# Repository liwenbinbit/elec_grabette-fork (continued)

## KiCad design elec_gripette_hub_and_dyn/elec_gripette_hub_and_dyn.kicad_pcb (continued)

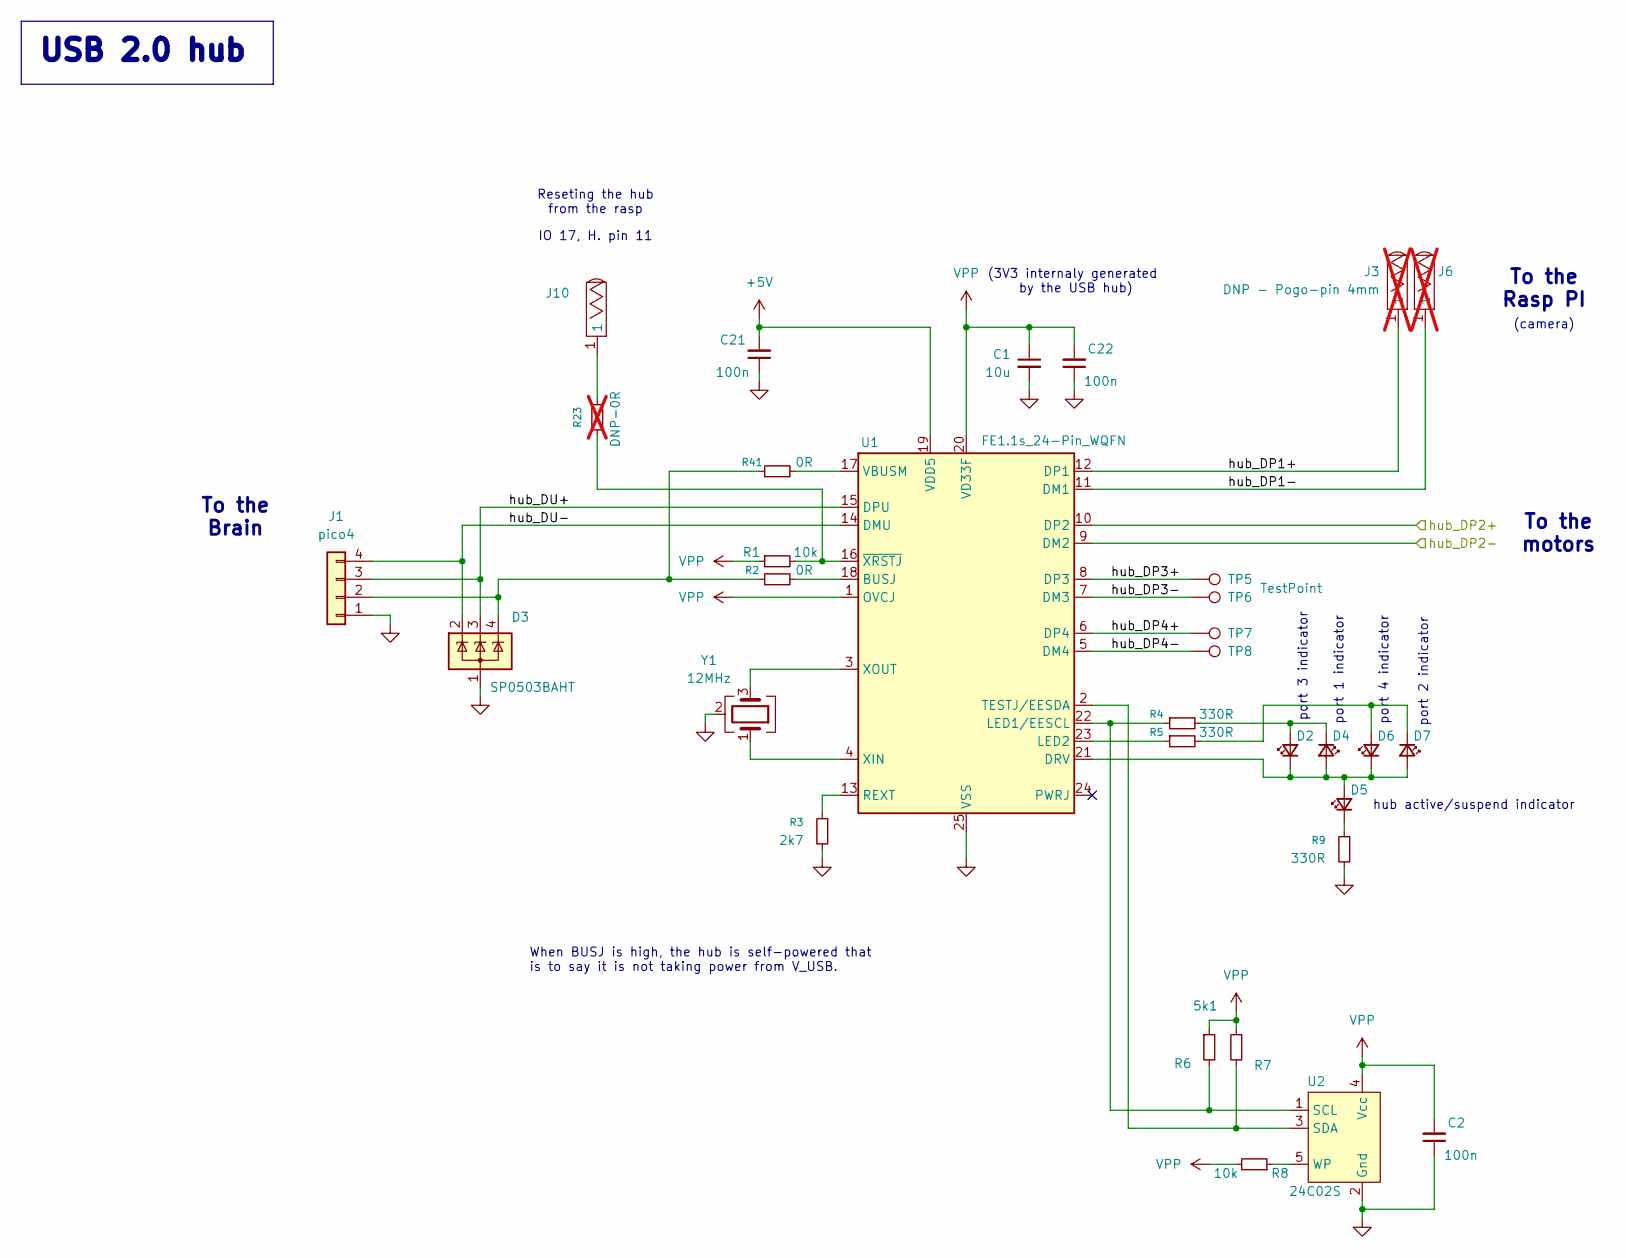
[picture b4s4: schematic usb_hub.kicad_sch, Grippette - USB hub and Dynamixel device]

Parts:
C1: 10u; C_0603_1608Metric; LCSC Part C1691
C2, C21, C22: 100n; C_0603_1608Metric; LCSC Part C85864
D2, D4, D6, D7: LED_Small; LED_0603_1608Metric; LCSC Part C7429915
D3: SP0503BAHT; SOT-143; LCSC Part C41364459
D5: LED_Small; LED_0603_1608Metric; LCSC Part C19171301
J1: pico4; Molex_PicoBlade_53047-0410_1x04_P1.25mm_Vertical; LCSC Part C504989
J3, J6: DNP - Pogo-pin 4mm; CONN-TH_YZ95315064P-01_pogo; LCSC Part C5157245; not fitted
J10: Pogo-pin 4mm; CONN-TH_YZ95315064P-01_pogo; LCSC Part C5157245
R1, R8: 10k; R_0402_1005Metric; LCSC Part C25744
R2, R41: 0R; R_0402_1005Metric; LCSC Part C17168
R3: 2k7; R_0402_1005Metric; LCSC Part C138017
R4, R5, R9: 330R; R_0402_1005Metric; LCSC Part C105875
R6, R7: 5k1; R_0402_1005Metric; LCSC Part C25905
R23: DNP-0R; R_0603_1608Metric; not fitted
TP5, TP6, TP7, TP8: TestPoint; TestPoint_Pad_D1.0mm
U1: FE1.1s_24-Pin_WQFN; WQFN-24-1EP_4x4mm_P0.5mm_EP2.6x2.6mm; LCSC Part C6776948
U2: 24C02S; SOT-23-5; LCSC Part C18723540
Y1: 12MHz; Crystal_SMD_3225-4Pin_3.2x2.5mm; LCSC Part C133334

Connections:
+5V: C21.2, U1.19 (VDD5); also elsewhere on the board
/Dynamixel-TTL over USB/hub_DP2+: U1.10 (DP2); also elsewhere on the board
/Dynamixel-TTL over USB/hub_DP2-: U1.9 (DM2); also elsewhere on the board
/USB hub/hub_DP1+: J3.1, U1.12 (DP1)
/USB hub/hub_DP1-: J6.1, U1.11 (DM1)
/USB hub/hub_DP3+: TP5.1, U1.8 (DP3)
/USB hub/hub_DP3-: TP6.1, U1.7 (DM3)
/USB hub/hub_DP4+: TP7.1, U1.6 (DP4)
/USB hub/hub_DP4-: TP8.1, U1.5 (DM4)
/USB hub/hub_DU+: D3.3 (K), J1.3, U1.15 (DPU)
/USB hub/hub_DU-: D3.2 (K), J1.4, U1.14 (DMU)
GND: C1.2, C2.1, C21.1, C22.1, D3.1 (A), J1.1, R3.2, R9.2, U1.25 (VSS), U2.2 (Gnd), Y1.2 (G), Y1.4 (G); also elsewhere on the board
unnamed: D2.2 (A), D4.1 (K), R4.2
unnamed: D2.1 (K), D4.2 (A), D5.2 (A), D6.1 (K), D7.2 (A), U1.21 (DRV)
unnamed: D5.1 (K), R9.1
unnamed: D6.2 (A), D7.1 (K), R5.2
unnamed: D3.4 (K), J1.2, R2.1, R41.1
unnamed: J10.1, R23.2
unnamed: R2.2, U1.18 (BUSJ)
unnamed: R4.1, R6.2, U1.22 (LED1/EESCL), U2.1 (SCL)
unnamed: R5.1, U1.23 (LED2)
unnamed: R3.1, U1.13 (REXT)
unnamed: R7.2, U1.2 (TESTJ/EESDA), U2.3 (SDA)
unnamed: R41.2, U1.17 (VBUSM)
unnamed: U1.4 (XIN), Y1.1
unnamed: U1.3 (XOUT), Y1.3
unnamed: R1.2, R23.1, U1.16 (~XRSTJ)
unnamed: R8.1, U2.5 (WP)
VPP: C1.1, C2.2, C22.2, R1.1, R6.1, R7.1, R8.2, U1.1 (OVCJ), U1.20 (VD33F), U2.4 (Vcc)

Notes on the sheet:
To the motors
port 4 indicator
When BUSJ is high, the hub is self-powered that is to say it is not taking power from V_USB.
port 2 indicator
port 3 indicator
To the Rasp PI
(3V3 internaly generated by the USB hub)
Reseting the hub from the rasp
(camera)
port 1 indicator
IO 17, H. pin 11
hub active/suspend indicator
To the Brain
USB 2.0 hub

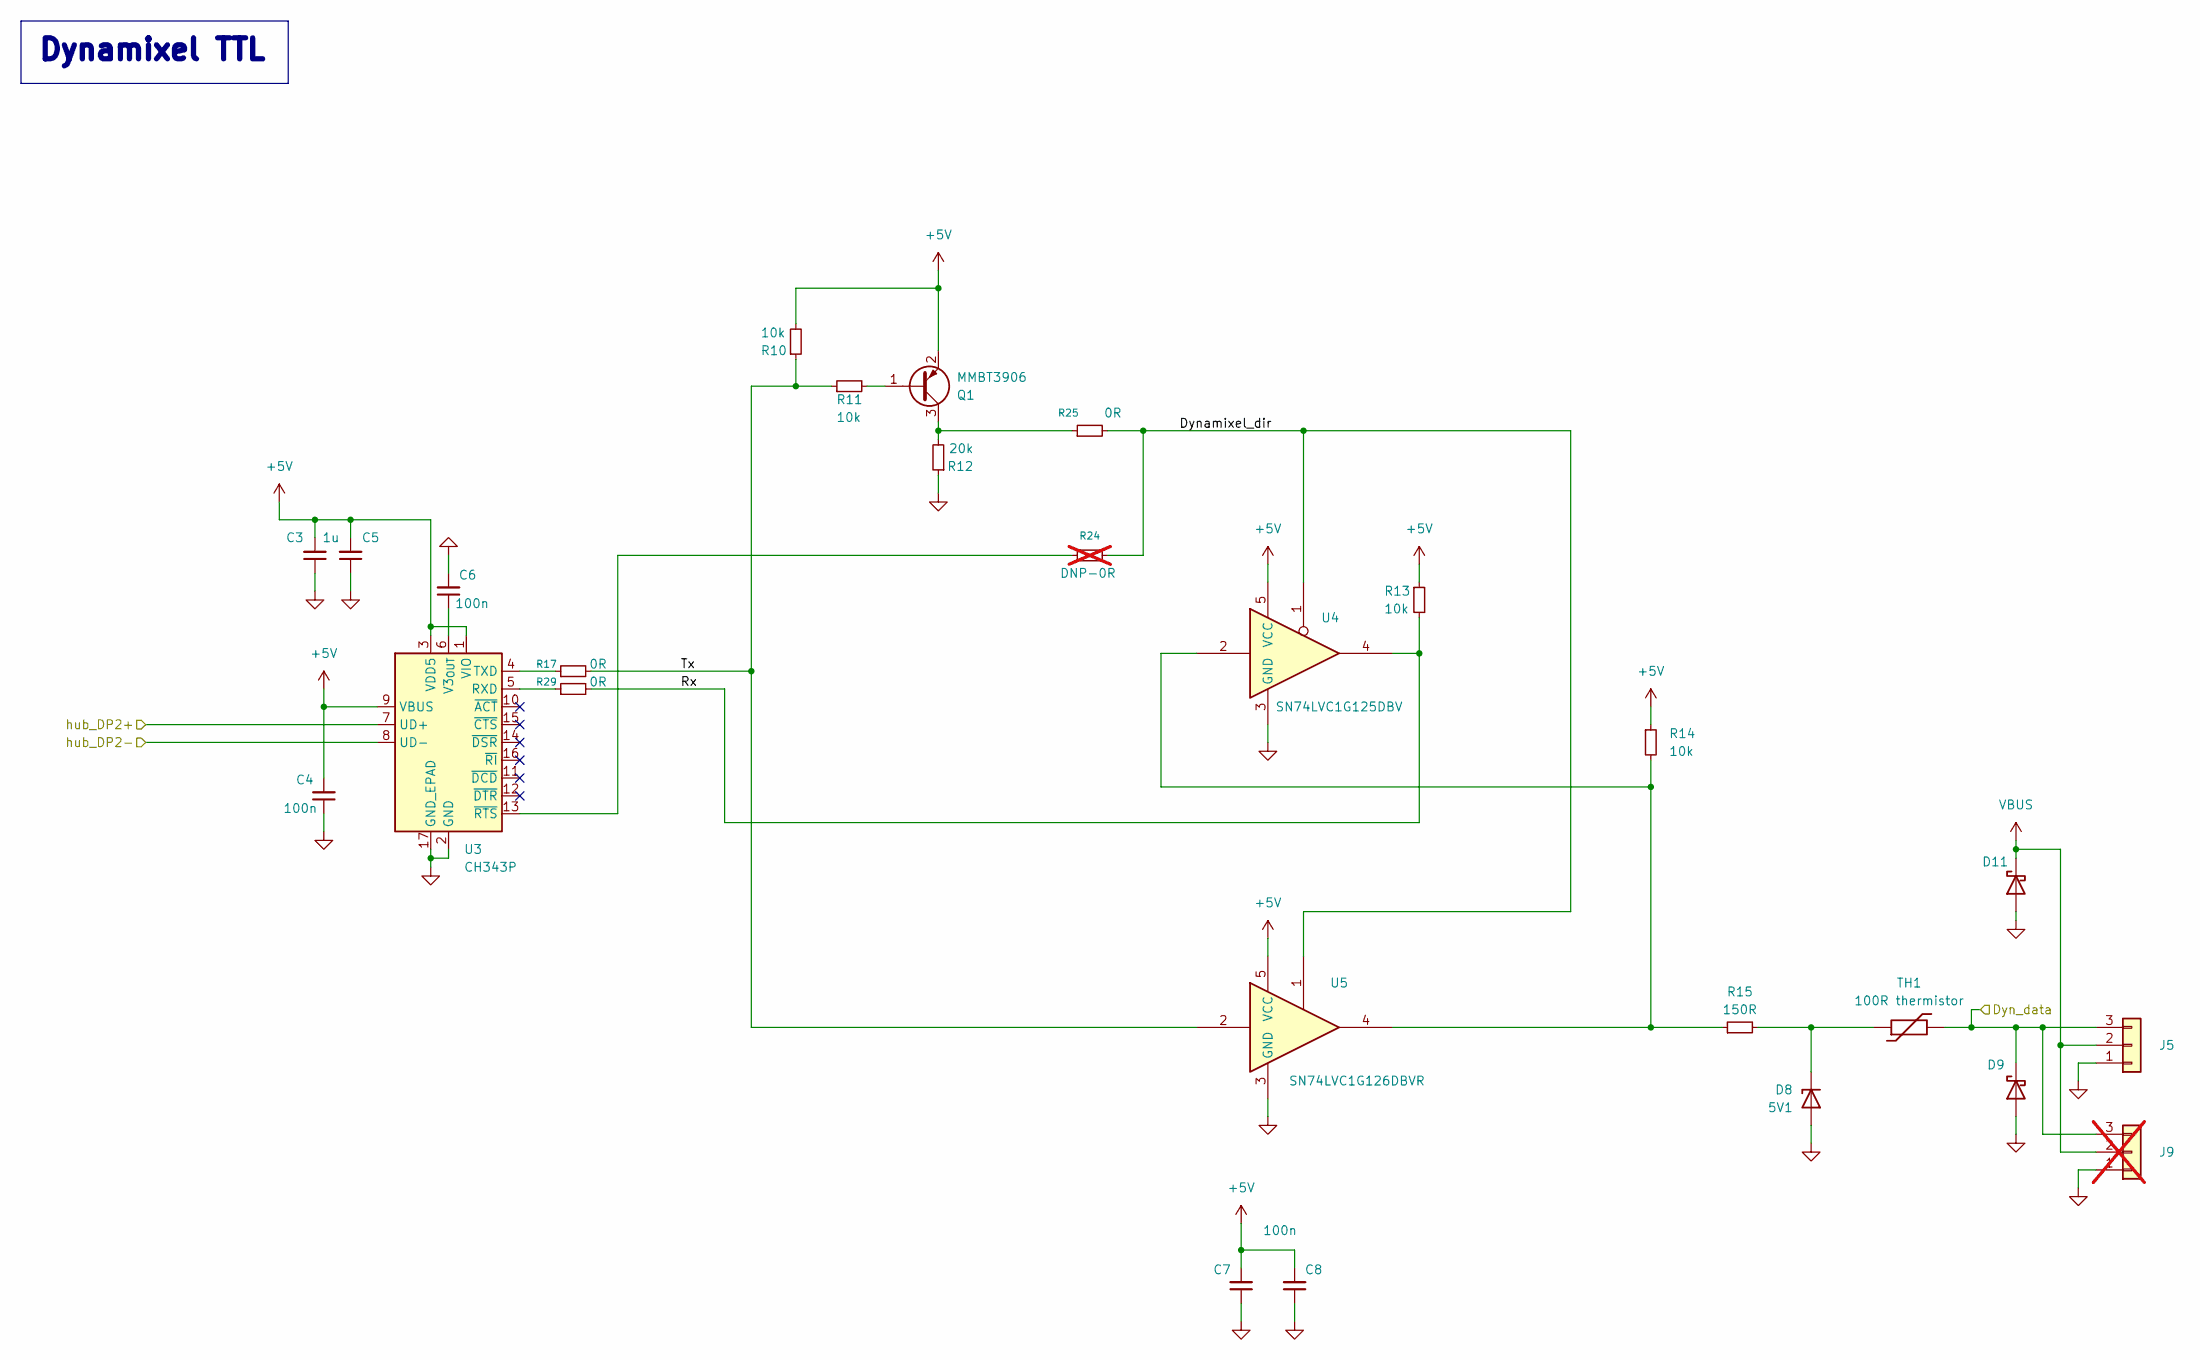
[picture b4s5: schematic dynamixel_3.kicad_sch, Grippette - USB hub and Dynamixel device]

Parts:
C3, C5: 1u; C_0603_1608Metric; LCSC Part C1592
C4, C6, C7, C8: 100n; C_0603_1608Metric; LCSC Part C85864
D8: 5V1; D_SOD-323; LCSC Part C151348
D9, D11: B5819WS; D_SOD-323; LCSC Part C64886
J5: Feetech; Molex_SPOX_5267-03A_1x03_P2.50mm_Vertical; LCSC Part C293315
J9: Feetech; Molex_SPOX_5267-03A_1x03_P2.50mm_Vertical; not fitted
Q1: MMBT3906; SOT-23; LCSC Part C727128
R10, R11, R13, R14: 10k; R_0402_1005Metric; LCSC Part C25744
R12: 20k; R_0402_1005Metric; LCSC Part C2906867
R15: 150R; R_0402_1005Metric; LCSC Part C138054
R17, R25, R29: 0R; R_0402_1005Metric; LCSC Part C17168
R24: DNP-0R; R_0603_1608Metric; not fitted
TH1: 100R thermistor; R_0603_1608Metric; LCSC Part C913703
U3: CH343P; WCH_QFN-16-1EP_3x3mm_P0.5mm_EP1.8x1.8mm; LCSC Part C2846043
U4: SN74LVC1G125DBV; SOT-23-5; LCSC Part C23654
U5: SN74LVC1G126DBVR; SOT-23-5; LCSC Part C7834

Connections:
+5V: C3.2, C4.2, C5.2, C7.2, C8.2, Q1.2 (E), R10.2, R13.1, R14.1, U3.1 (VIO), U3.3 (VDD5), U3.9 (VBUS), U4.5 (VCC), U5.5 (VCC); also elsewhere on the board
/Dynamixel-TTL over USB/Dyn_data: D9.1 (K), J5.3, J9.3, TH1.2; also elsewhere on the board
/Dynamixel-TTL over USB/Dynamixel_dir: R24.2, R25.2, U4.1, U5.1
/Dynamixel-TTL over USB/Rx: R13.2, R29.2, U4.4
/Dynamixel-TTL over USB/Tx: R10.1, R11.1, R17.2, U5.2
/Dynamixel-TTL over USB/hub_DP2+: U3.7 (UD+); also elsewhere on the board
/Dynamixel-TTL over USB/hub_DP2-: U3.8 (UD-); also elsewhere on the board
GND: C3.1, C4.1, C5.1, C6.2, C7.1, C8.1, D8.2 (A), D9.2 (A), D11.2 (A), J5.1, J9.1, R12.1, U3.2 (GND), U3.17 (GND_EPAD), U4.3 (GND), U5.3 (GND); also elsewhere on the board
unnamed: D8.1 (K), R15.2, TH1.1
unnamed: Q1.1 (B), R11.2
unnamed: Q1.3 (C), R12.2, R25.1
unnamed: R14.2, R15.1, U4.2, U5.4
unnamed: R29.1, U3.5 (RXD)
unnamed: R17.1, U3.4 (TXD)
unnamed: C6.1, U3.6 (V3_{OUT})
unnamed: R24.1, U3.13 (~RTS)
VBUS: D11.1 (K), J5.2, J9.2; also elsewhere on the board

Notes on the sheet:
Dynamixel TTL

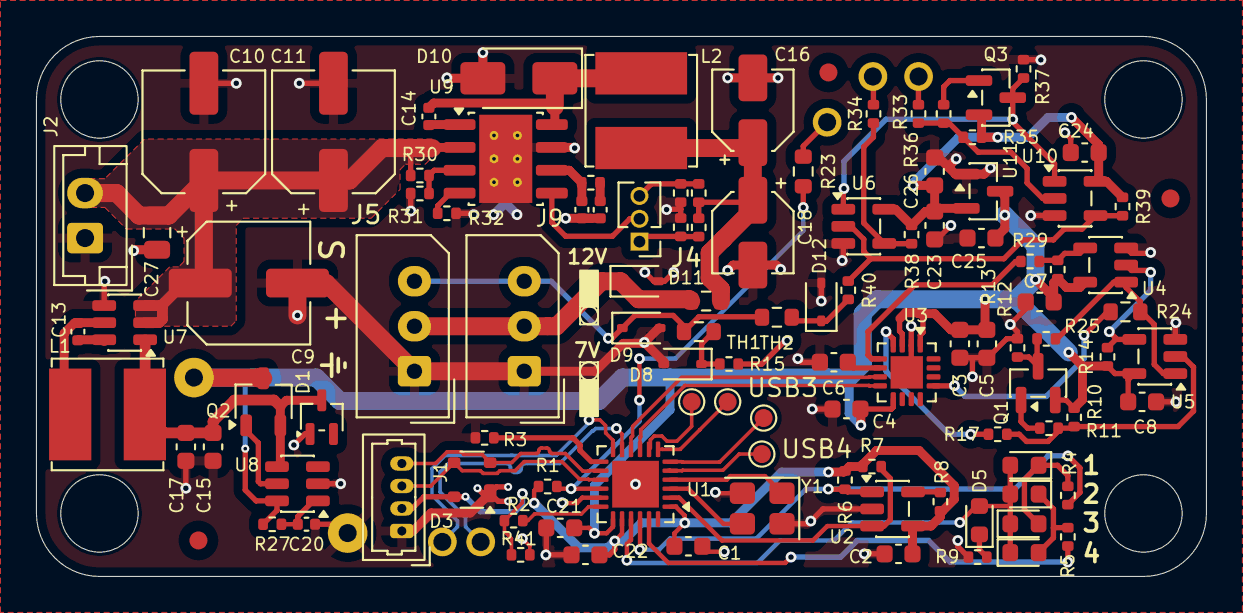
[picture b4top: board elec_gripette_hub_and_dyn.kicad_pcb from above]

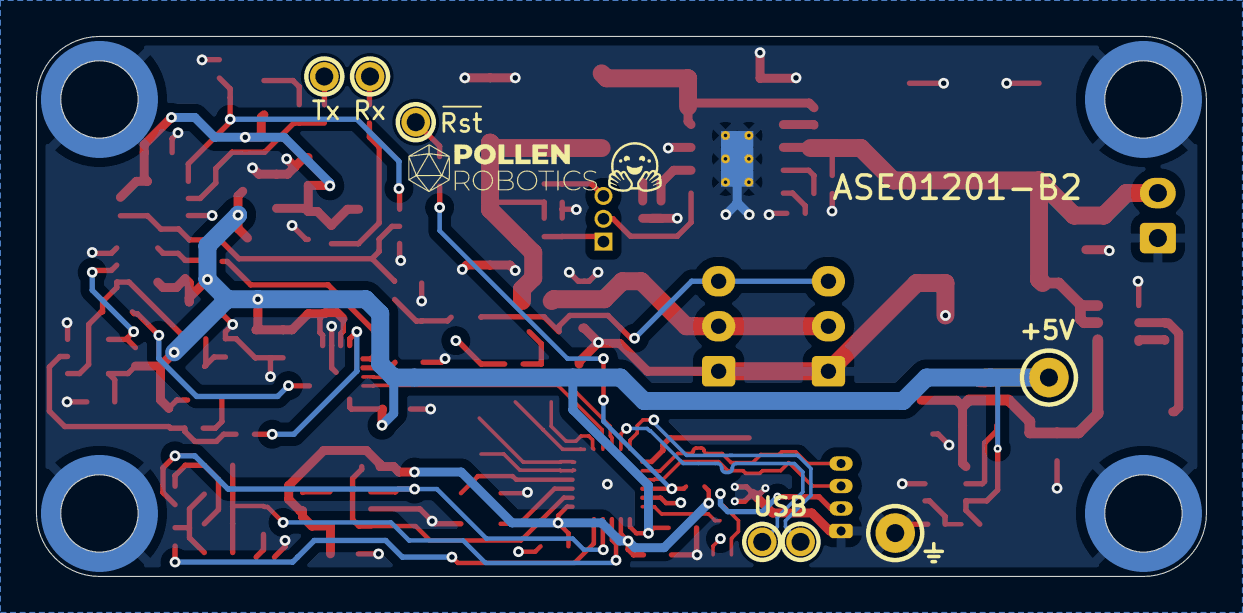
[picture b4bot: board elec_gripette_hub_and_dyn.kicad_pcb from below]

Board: 4 copper layers, 65.0 x 30.0 mm, 122 parts (13 on the bottom side), 67 nets.

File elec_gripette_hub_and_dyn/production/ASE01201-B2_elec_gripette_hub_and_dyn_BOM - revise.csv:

Designator,Footprint,Quantity,Value,LCSC Part #
C1,0603,1,10u,C1691
"C10, C11, C9",CP_Elec_6.3x7.7,3,10u 35V,C72488
C12,0402,1,4n7,C1518204
"C13, C14",0402,2,100n,C307331
"C15, C17",0603,2,22u 6V3,C84419
"C16, C18",CP_Elec_4x5.4,2,22u 16V,C72502
C19,0402,1,47p,C1567
"C2, C21, C22, C23, C24, C4, C6, C7, C8",0603,9,100n,C85864
C20,0402,1,100n 6V3,C1525
"C25, C26, C3, C5",0603,4,1u,C1592
C27,0805,1,"3,3u 35V",C361184
D1,SOT-323_SC-70,1,BAT54W,C78606
D10,D_SMA,1,D_Schottky 3A,C8678
"D11, D9",D_SOD-323,2,B5819WS,C64886
"D12, D8",D_SOD-323,2,5V1,C151348
"D2, D4, D6, D7",0603,4,LED_Small,C7429915
D3,SOT-143,1,SP0503BAHT,C41364459
D5,0603,1,LED_Small,C19171301
"H4, H5, H6, H7",SMD_BD5.6-D4.1_spacer,4,"M2,5 x 4mm spacer",C2916324
J1,Molex_PicoBlade_53047-0410_1x04_P1.25mm_Vertical,1,pico4,C504989
"J10, J13, J14",CONN-TH_YZ95315064P-01_pogo,3,Pogo-pin 4mm,C5157245
J2,JST_EH_B2B-EH-A_1x02_P2.50mm_Vertical,1,JST EH 2,C160262
,,,,
J4,PinHeader_1x03_P1.27mm_Vertical,1,Header 3,C7470079
J5,Molex_SPOX_5267-03A_1x03_P2.50mm_Vertical,1,Feetech,C293315
"J7, J8",CONN-TH_YZ08415060P-02_pogo,2,Pogo-pin 2A 4mm,C7471674
,,,,
"L1, L2",L_Bourns_SRN6045TA,2,"6,8u 3A",C57254
"Q1, Q3",SOT-23,2,MMBT3906,C727128
Q2,TSOT-23,1,SI2312CDS-T1-GE3,C142518
"R1, R10, R11, R13, R14, R35, R36, R38, R39, R8",0402,10,10k,C25744
"R12, R37",0402,2,20k,C2906867
"R15, R40",0402,2,150R,C138054
R16,0402,1,100k,C2906883
"R17, R2, R25, R29, R33, R34, R41",0402,7,0R,C17168
R18,0402,1,16k9,C25858
R21,0402,1,62k,C2909375
R22,0402,1,8k2,C25924
,,,,
R26,0402,1,7k5,C25918
R27,0402,1,100R,C2906860
R28,0603,1,0R,C21189
R3,0402,1,2k7,C138017
,,,,
R32,0402,1,243k,C43249
"R4, R5, R9",0402,3,330R,C105875
"R6, R7",0402,2,5k1,C25905
"TH1, TH2",0603,2,100R thermistor,C913703
,,,,
U1,WQFN-24-1EP_4x4mm_P0.5mm_EP2.6x2.6mm,1,FE1.1s_24-Pin_WQFN,C6776948
"U10, U5",SOT-23-5,2,SN74LVC1G126DBVR,C7834
U11,SOT-23,1,MCP1700x-330xxTT,C39051
U2,SOT-23-5,1,24C02S,C18723540
U3,WCH_QFN-16-1EP_3x3mm_P0.5mm_EP1.8x1.8mm,1,CH343P,C2846043
"U4, U6",SOT-23-5,2,SN74LVC1G125DBV,C23654
U7,TSOT-23-6,1,AP63205,C2071056
U8,TSOT-23-6,1,LM5050-1,C473393
U9,Texas_R-PDSO-G8_EP2.95x4.9mm_Mask2.4x3.1mm_ThermalVias,1,TPS54560BDDA,C1850354
Y1,Crystal_SMD_3225-4Pin_3.2x2.5mm,1,12MHz,C133334

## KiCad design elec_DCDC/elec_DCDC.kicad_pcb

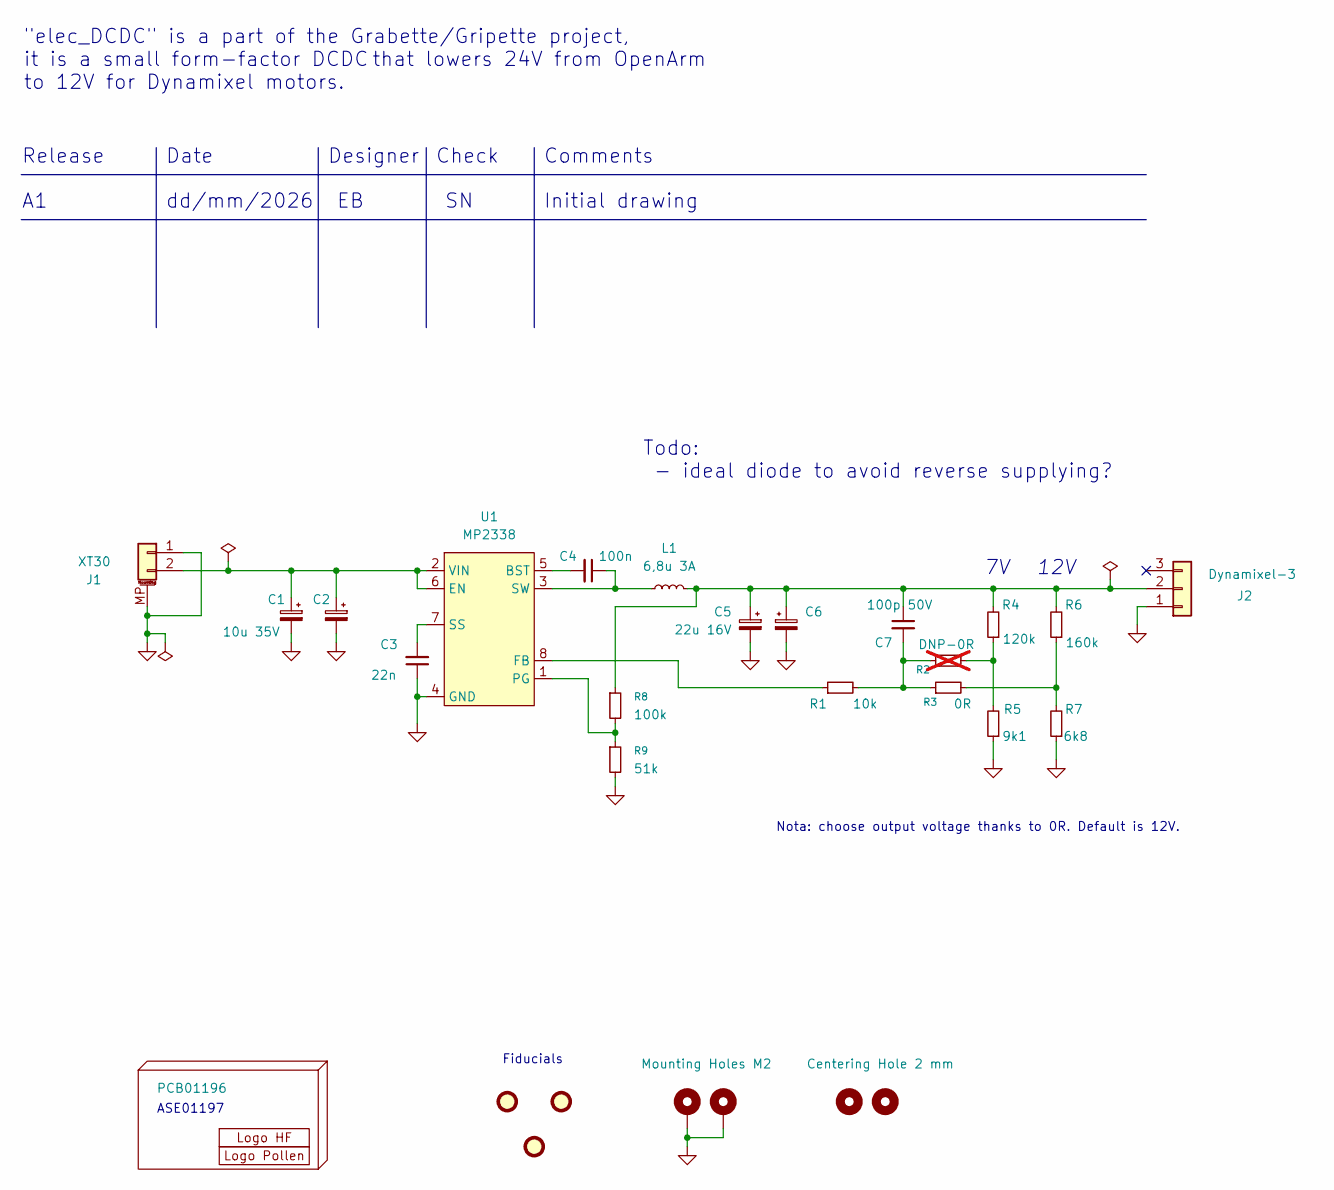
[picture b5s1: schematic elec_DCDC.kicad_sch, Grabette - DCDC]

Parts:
C1, C2: 10u 35V; CP_Elec_6.3x7.7; LCSC Part C72488
C3: 22n; C_0402_1005Metric; LCSC Part C1532
C4: 100n; C_0402_1005Metric; LCSC Part C307331
C5, C6: 22u 16V; CP_Elec_4x5.4; LCSC Part C72502
C7: 100p 50V; C_0402_1005Metric; LCSC Part C106200
FID1, FID2, FID3: DNP Fiducial; Fiducial_1mm_Mask2mm
H1: PCB01196
H2: Logo HF 2025; Logo_HF_2025
H3: DNP Logo Pollen 2021; Logo_Pollen_2021_sq
H4, H5: Mounting Holes M2; MountingHole_2.2mm_M2_ISO7380_Pad_TopBottom
H6, H7: Centering Hole 2 mm; MountingHole_2.0mm
J1: XT30; AMASS_XT30PW-M_1x02_P2.50mm_Horizontal; LCSC Part C431092
J2: Dynamixel-3; JST_EH_B3B-EH-A_1x03_P2.50mm_Vertical; LCSC Part C160259
L1: 6,8u 3A; L_Bourns_SRN6045TA; LCSC Part C57254
R1: 10k; R_0402_1005Metric; LCSC Part C25744
R2: DNP-0R; R_0402_1005Metric; LCSC Part C17168; not fitted
R3: 0R; R_0402_1005Metric; LCSC Part C17168
R4: 120k; R_0402_1005Metric; LCSC Part C2909314
R5: 9k1; R_0402_1005Metric; LCSC Part C2909390
R6: 160k; R_0402_1005Metric; LCSC Part C25757
R7: 6k8; R_0402_1005Metric; LCSC Part C2906876
R8: 100k; R_0402_1005Metric; LCSC Part C2906883
R9: 51k; R_0402_1005Metric; LCSC Part C2909367
U1: MP2338; SOT-583-8_L2.1-W1.2-P0.50-LS1.6-BR; LCSC Part C7210174

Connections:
GND: C1.2, C2.2, C3.1, C5.2, C6.2, H4.1, H5.1, J1.1, J1.MP (MountPin), J2.1, R5.1, R7.1, R9.2, U1.4 (GND)
unnamed: C7.2, R1.2, R2.1, R3.1
unnamed: C1.1, C2.1, J1.2, U1.2 (VIN), U1.6 (EN)
unnamed: C5.1, C6.1, C7.1, J2.2, L1.1, R4.2, R6.2, R8.1
unnamed: R2.2, R4.1, R5.2
unnamed: R3.2, R6.1, R7.2
unnamed: C4.2, U1.5 (BST)
unnamed: R1.1, U1.8 (FB)
unnamed: R8.2, R9.1, U1.1 (PG)
unnamed: C3.2, U1.7 (SS)
unnamed: C4.1, L1.2, U1.3 (SW)

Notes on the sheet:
Date
Check
Release
Fiducials
ASE01197
12V
Initial drawing
"elec_DCDC" is a part of the Grabette/Gripette project, it is a small form-factor DCDC that lowers 24V from OpenArm to 12V for Dynamixel motors.
Todo: - ideal diode to avoid reverse supplying?
Nota: choose output voltage thanks to 0R. Default is 12V.
Designer
Comments
dd/mm/2026

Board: 2 copper layers, 29 parts (2 on the bottom side), 11 nets, no tracks yet.

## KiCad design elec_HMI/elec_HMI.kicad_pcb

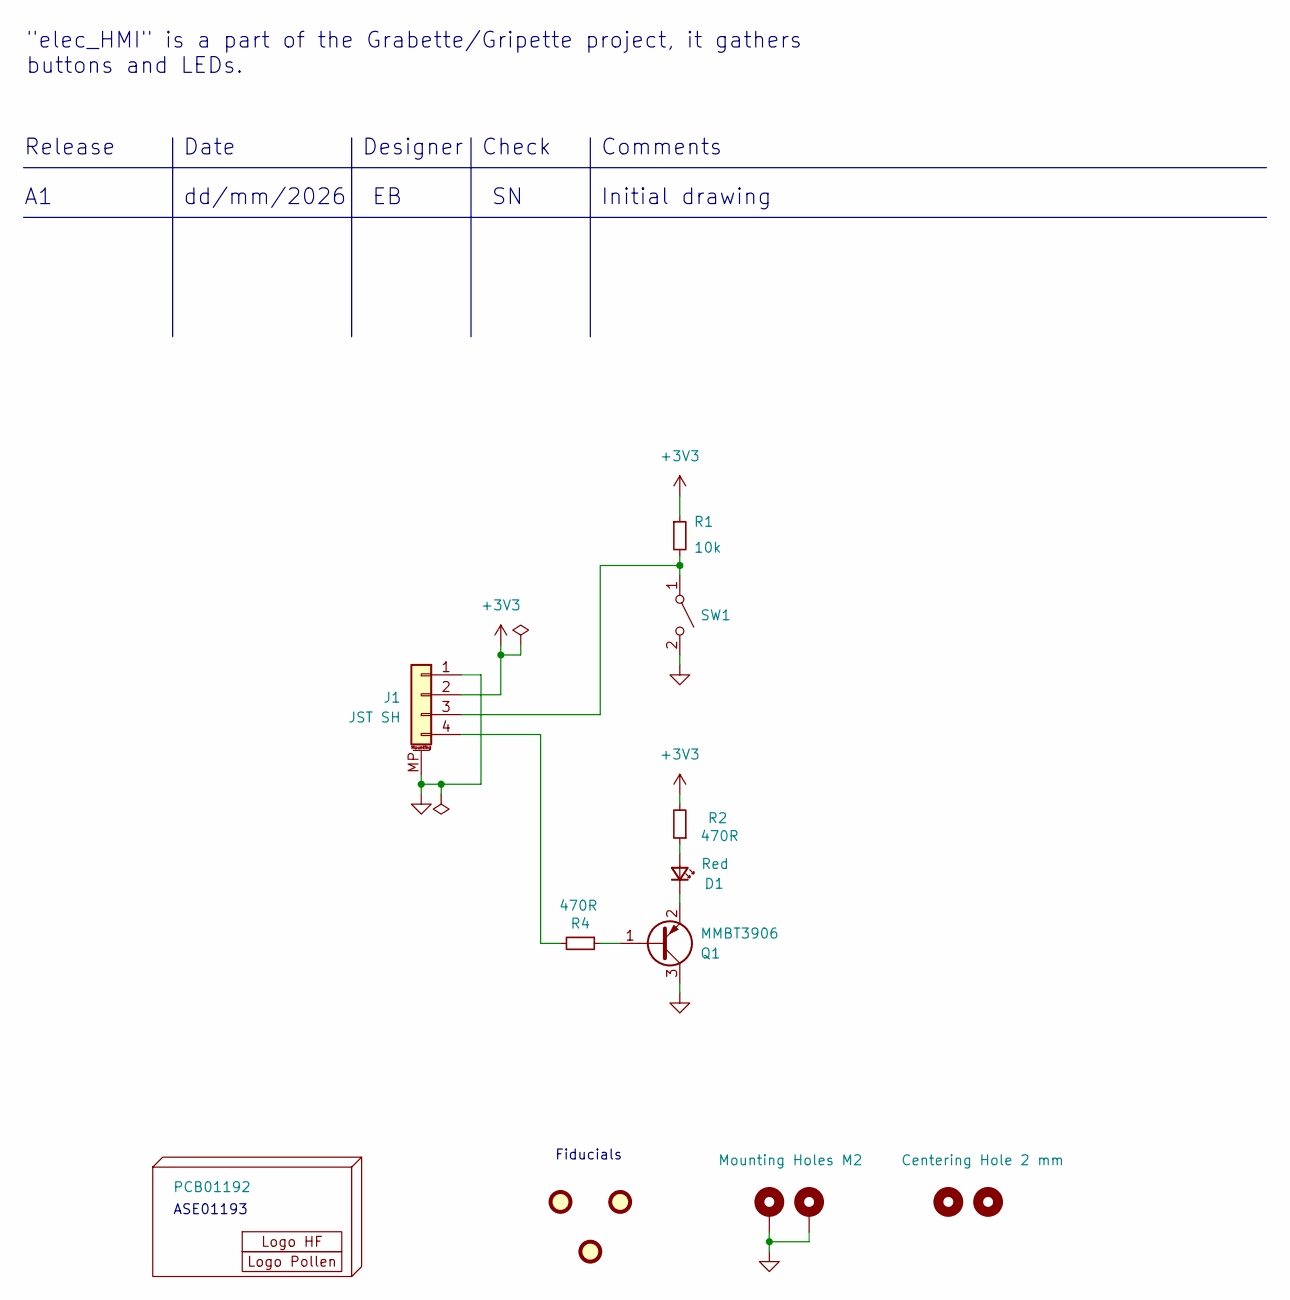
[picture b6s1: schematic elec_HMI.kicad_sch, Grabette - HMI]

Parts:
D1: Red; LED_0603_1608Metric; LCSC Part C84263
FID1, FID2, FID3: DNP Fiducial; Fiducial_1mm_Mask2mm
H1: PCB01192
H2: Logo HF 2025; Logo_HF_2025
H3: DNP Logo Pollen 2021; Logo_Pollen_2021_sq
H4, H5: Mounting Holes M2; MountingHole_2.2mm_M2_ISO7380_Pad_TopBottom
H6, H7: Centering Hole 2 mm; MountingHole_2.0mm
J1: JST SH; JST_SH_SM04B-SRSS-TB_1x04-1MP_P1.00mm_Horizontal; LCSC Part C160404
Q1: MMBT3906; SOT-23; LCSC Part C727128
R1: 10k; R_0402_1005Metric; LCSC Part C25744
R2, R4: 470R; R_0402_1005Metric; LCSC Part C25117
SW1: SW_SPST; KEY-TH_CPG135001D0X; LCSC Part C400229

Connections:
+3V3: J1.2, R1.1, R2.2
GND: H4.1, H5.1, J1.1, J1.MP (MountPin), Q1.3 (C), SW1.2 (B)
unnamed: D1.2 (A), R2.1
unnamed: D1.1 (K), Q1.2 (E)
unnamed: J1.3, R1.2, SW1.1 (A)
unnamed: J1.4, R4.2
unnamed: Q1.1 (B), R4.1

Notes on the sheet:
Date
Check
Release
Fiducials
ASE01193
Initial drawing
"elec_HMI" is a part of the Grabette/Gripette project, it gathers buttons and LEDs.
Designer
Comments
dd/mm/2026

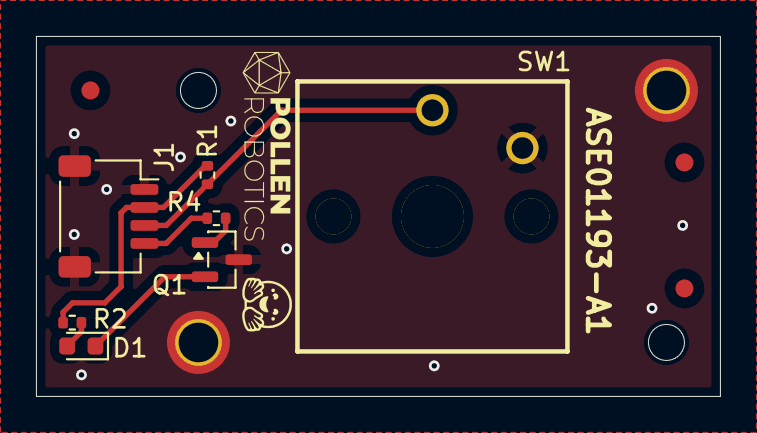
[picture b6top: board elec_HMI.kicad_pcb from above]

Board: 2 copper layers, 38.0 x 20.0 mm, 16 parts (0 on the bottom side), 7 nets.

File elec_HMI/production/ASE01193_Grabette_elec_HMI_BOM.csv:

Designator,Footprint,Quantity,Value,LCSC Part #
D1,0603,1,Red,C84263
H2,Logo_HF_2025,1,Logo HF 2025,
J1,JST_SH_SM04B-SRSS-TB_1x04-1MP_P1.00mm_Horizontal,1,JST SH,C160404
Q1,SOT-23,1,MMBT3906,C727128
R1,0402,1,10k,C25744
"R2, R4",0402,2,470R,C25117
SW1,SW_Cherry_MX_1.00u_PCB,1,SW_SPST,C400229

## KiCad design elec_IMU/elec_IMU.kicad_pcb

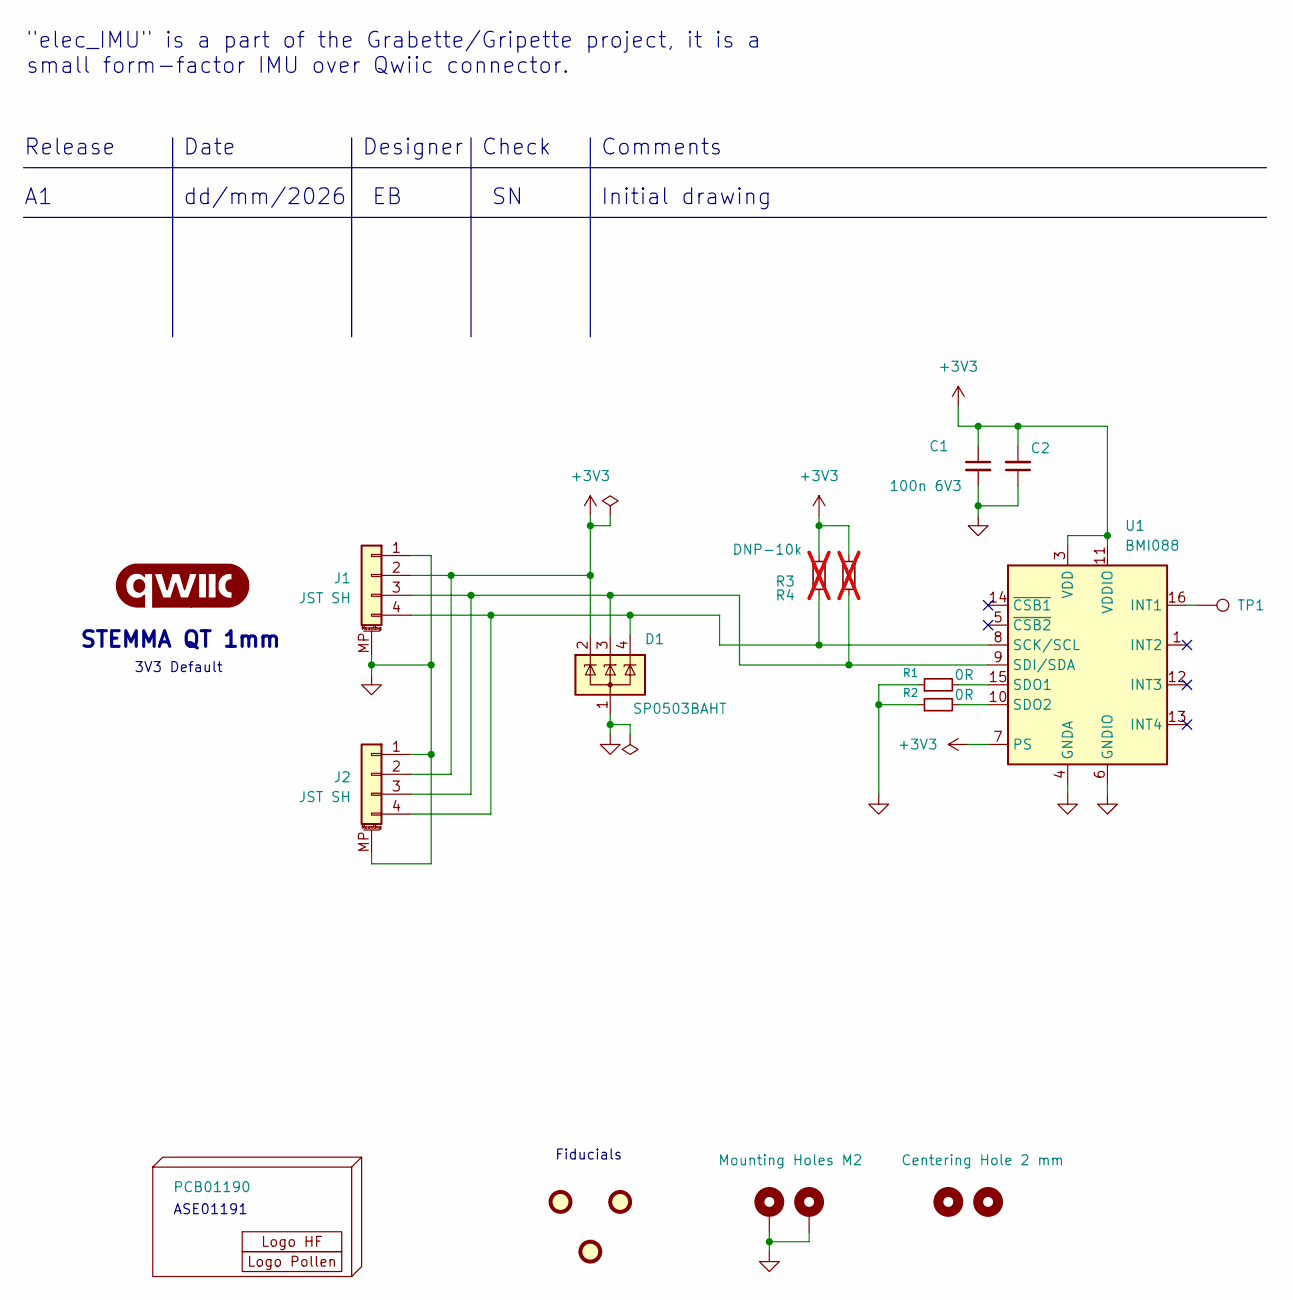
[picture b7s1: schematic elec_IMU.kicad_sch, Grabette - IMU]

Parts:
C1, C2: 100n 6V3; C_0402_1005Metric; LCSC Part C1525
D1: SP0503BAHT; SOT-143; LCSC Part C41364459
FID1, FID2, FID3: DNP Fiducial; Fiducial_1mm_Mask2mm
G1: qwiic_Logo; Logo_qwiic_5mm
H1: PCB01190
H2: Logo HF 2025; Logo_HF_2025
H3: DNP Logo Pollen 2021; Logo_Pollen_2021_sq
H4, H5: Mounting Holes M2; MountingHole_2.2mm_M2_ISO7380_Pad_TopBottom
H6, H7: Centering Hole 2 mm; MountingHole_2.0mm
J1, J2: JST SH; JST_SH_SM04B-SRSS-TB_1x04-1MP_P1.00mm_Horizontal; LCSC Part C160404
R1, R2: 0R; R_0402_1005Metric; LCSC Part C17168
R3, R4: DNP-10k; R_0402_1005Metric; LCSC Part C25744; not fitted
TP1: TestPoint; TestPoint_Loop_D2.50mm_Drill1.0mm_LowProfile
U1: BMI088; Bosch_LGA-16_4.5x3mm_P0.5mm_LayoutBorder7x1y_ClockwisePinNu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; LCSC Part C194919

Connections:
+3V3: C1.1, C2.2, D1.2 (K), J1.2, J2.2, R3.1, R4.1, U1.3 (VDD), U1.7 (PS), U1.11 (VDDIO)
GND: C1.2, C2.1, D1.1 (A), H4.1, H5.1, J1.1, J1.MP (MountPin), J2.1, J2.MP (MountPin), R1.1, R2.1, U1.2 (GNDA), U1.4 (GNDA), U1.6 (GNDIO)
unnamed: D1.3 (K), J1.3, J2.3, R4.2, U1.9 (SDI/SDA)
unnamed: D1.4 (K), J1.4, J2.4, R3.2, U1.8 (SCK/SCL)
unnamed: TP1.1, U1.16 (INT1)
unnamed: R1.2, U1.15 (SDO1)
unnamed: R2.2, U1.10 (SDO2)

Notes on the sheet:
Date
Check
Release
STEMMA QT 1mm
Fiducials
ASE01191
3V3 Default
Initial drawing
"elec_IMU" is a part of the Grabette/Gripette project, it is a small form-factor IMU over Qwiic connector.
Designer
Comments
dd/mm/2026

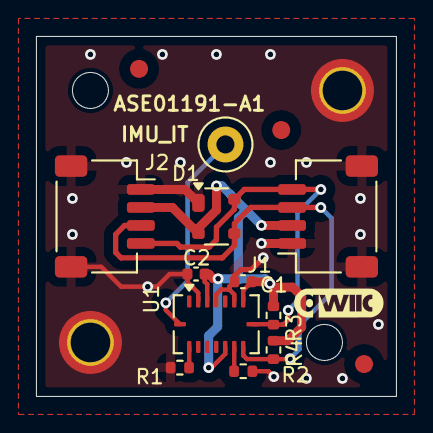
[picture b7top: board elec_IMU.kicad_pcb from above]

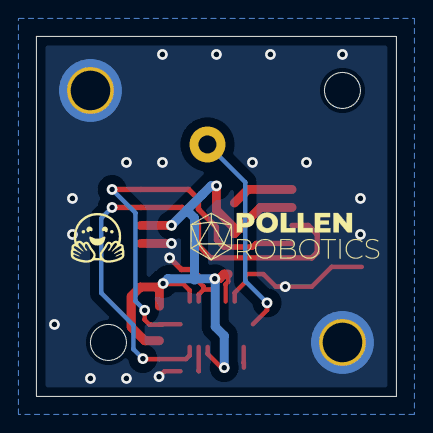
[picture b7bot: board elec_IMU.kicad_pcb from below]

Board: 2 copper layers, 20.0 x 20.0 mm, 21 parts (2 on the bottom side), 7 nets.

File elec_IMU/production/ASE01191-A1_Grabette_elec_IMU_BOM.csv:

Designator,Footprint,Quantity,Value,LCSC Part #
"C1, C2",0402,2,100n 6V3,C1525
D1,SOT-143,1,SP0503BAHT,C41364459
G1,Logo_qwiic_5mm,1,qwiic_Logo,
H2,Logo_HF_2025,1,Logo HF 2025,
"J1, J2",JST_SH_SM04B-SRSS-TB_1x04-1MP_P1.00mm_Horizontal,2,JST SH,C160404
"R1, R2",0402,2,0R,C17168
"R3, R4",0402,2,DNP-10k,C25744
TP1,TestPoint_Loop_D2.50mm_Drill1.0mm_LowProfile,1,TestPoint,
U1,Bosch_LGA-16_4.5x3mm_P0.5mm_LayoutBorder7x1y_ClockwisePinNumbering,1,BMI088,C194919

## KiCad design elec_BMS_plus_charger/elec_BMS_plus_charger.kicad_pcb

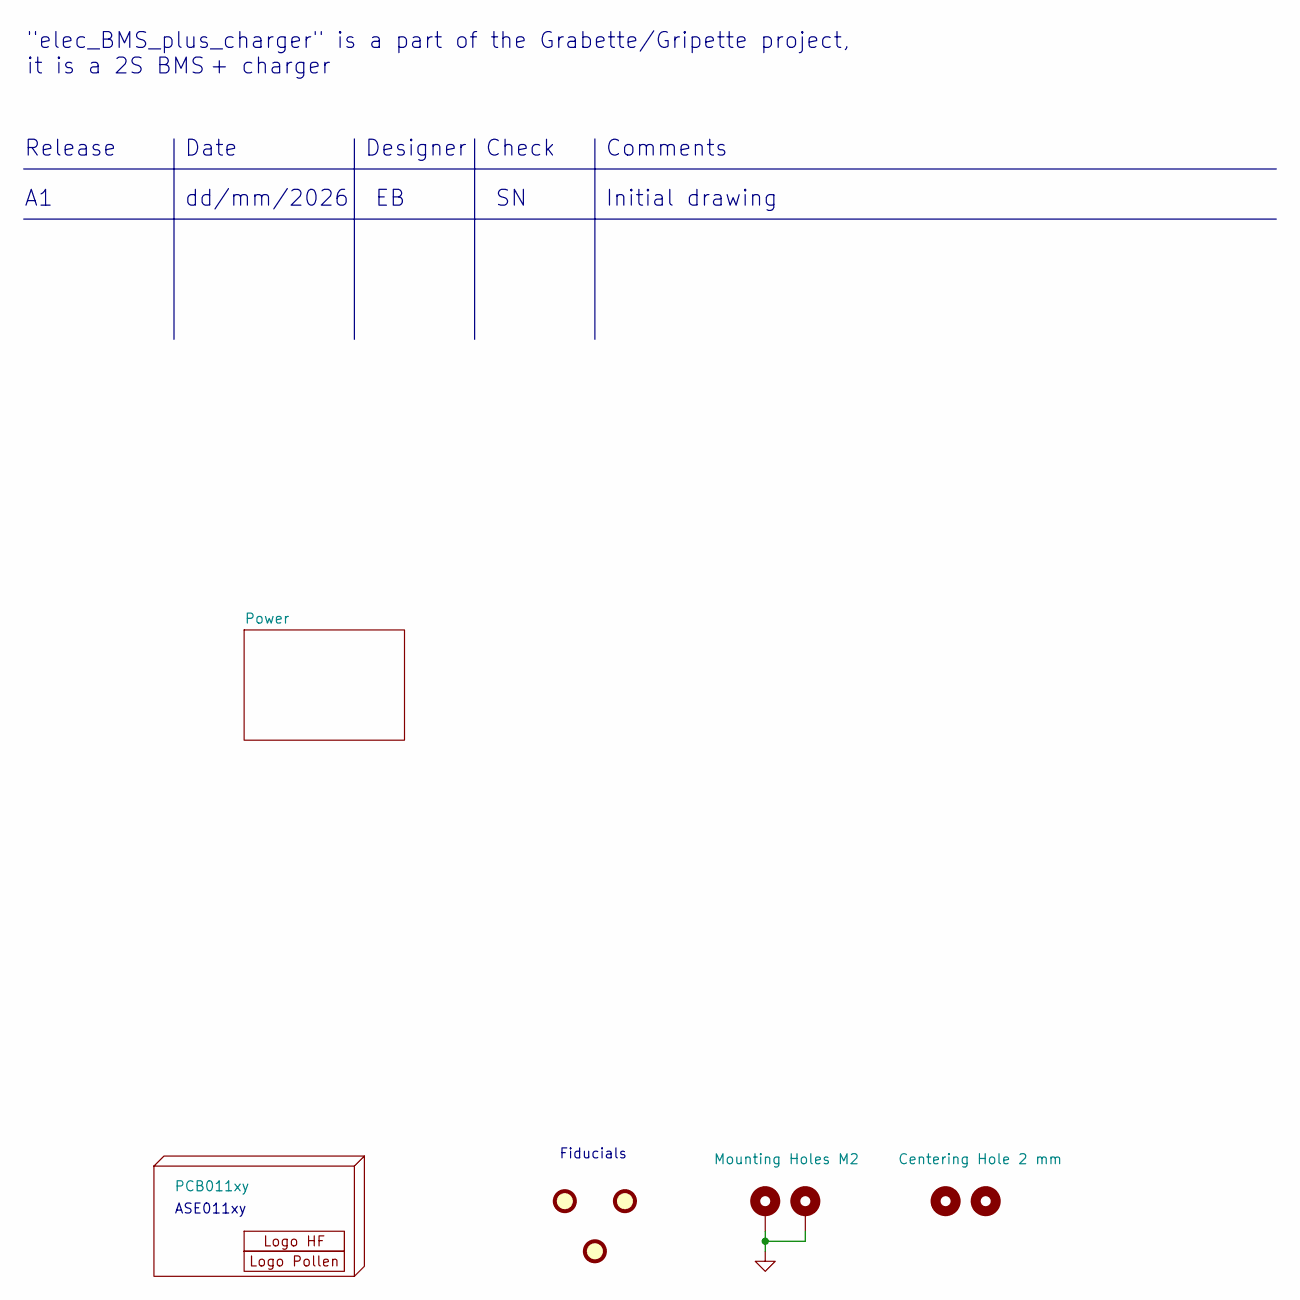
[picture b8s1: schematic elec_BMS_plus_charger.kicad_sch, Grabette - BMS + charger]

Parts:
FID1, FID2, FID3: DNP Fiducial; Fiducial_1mm_Mask2mm
H1: PCB011xy
H2: Logo HF 2025; Logo_HF_2025
H3: DNP Logo Pollen 2021; Logo_Pollen_2021_sq
H4, H5: Mounting Holes M2; MountingHole_2.2mm_M2_ISO7380_Pad_TopBottom
H6, H7: Centering Hole 2 mm; MountingHole_2.0mm

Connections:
GND: H4.1, H5.1, H6.1, H7.1; also elsewhere on the board

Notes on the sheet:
Date
Check
Release
Fiducials
ASE011xy
Initial drawing
"elec_BMS_plus_charger" is a part of the Grabette/Gripette project, it is a 2S BMS + charger
Designer
Comments
dd/mm/2026
